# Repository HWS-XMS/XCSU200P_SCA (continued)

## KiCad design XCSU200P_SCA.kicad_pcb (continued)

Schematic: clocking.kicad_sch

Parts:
C1001, C1002, C1003, C1004, C1005, C1009, C1012, C1015, C1018: 100n; C_0402_1005Metric; MPN Samsung CL05B104KO5NNNC, 16 V X7R; LCSC C1525
C1006: 100n; C_0402_1005Metric; MPN Samsung CL05B104KO5NNNC, 16 V X7R; LCSC C1525; not fitted
C1007, C1010, C1013, C1016: 4u7; C_0603_1608Metric; MPN Samsung CL10A475KO8NNNC, 16 V X5R; LCSC C19666
C1008, C1011, C1014, C1017: 470n; C_0402_1005Metric; MPN Samsung CL05A474KP5NNNC, 10 V X5R; LCSC C47339
D1001: BAT54; D_SOD-323; MPN onsemi BAT54HT1G; LCSC C21107
FB1001, FB1002, FB1003, FB1004: 600R@100MHz; L_0603_1608Metric; MPN Sunlord GZ1608D601TF, 200 mA; LCSC C1002
J1001: REF IN; SMA_Molex_73251-2200_Horizontal_Drill1.6mm; MPN Lian Xin SMA-KWE; LCSC C7498154
J1002: REF OUT; SMA_Molex_73251-2200_Horizontal_Drill1.6mm; MPN Lian Xin SMA-KWE; LCSC C7498154
JP1001: 50R term; PinHeader_1x02_P2.54mm_Vertical; MPN XFCN PZ254V-11-02P; LCSC C492401
JP1002: REFSEL = H; PinHeader_1x02_P2.54mm_Vertical; MPN XFCN PZ254V-11-02P; LCSC C492401
JP1003: HW_SW_CTRL; PinHeader_1x03_P2.54mm_Vertical; MPN BOOMELE 2.54-1*3P; LCSC C49257
JP1004: REF / FPGA; PinHeader_1x03_P2.54mm_Vertical; MPN BOOMELE 2.54-1*3P; LCSC C49257
R1001: 49R9 1W; R_2512_6332Metric; MPN UNI-ROYAL 25121WF499JT4E, 1 W; LCSC C25487
R1002: 330R; R_0402_1005Metric; MPN UNI-ROYAL 0402WGF3300TCE; LCSC C25104
R1003: 12k; R_0402_1005Metric; MPN UNI-ROYAL 0402WGF1202TCE; LCSC C25752
R1004, R1007, R1018: 10k; R_0402_1005Metric; MPN UNI-ROYAL 0402WGF1002TCE; LCSC C25744
R1005, R1008, R1009: 33R; R_0402_1005Metric; MPN UNI-ROYAL 0402WGF330JTCE; LCSC C25105
R1006: 100k; R_0402_1005Metric; MPN UNI-ROYAL 0402WGF1003TCE; LCSC C25741
R1010, R1011: 10R; R_0402_1005Metric; MPN UNI-ROYAL 0402WGF100JTCE; LCSC C25077
R1012: 100R; R_0402_1005Metric; MPN UNI-ROYAL 0402WGF1000TCE; LCSC C25076; not fitted
R1013, R1014, R1015: 1k; R_0402_1005Metric; MPN UNI-ROYAL 0402WGF1001TCE; LCSC C11702
R1016, R1017: 4k7; R_0402_1005Metric; MPN UNI-ROYAL 0402WGF4701TCE; LCSC C25900
R1019: 47R; R_0402_1005Metric; MPN UNI-ROYAL 0402WGF470JTCE; LCSC C25118
R1020: 100R; R_0402_1005Metric; MPN UNI-ROYAL 0402WGF1000TCE; LCSC C25076
SW1001: TCXO / EXT; SW_SPDT_Shouhan_MSK12C02; LCSC C431540
TP1001: OUT0; TestPoint_Keystone_5005-5009_Compact_NoCircle; MPN Keystone 5008 (orange)
TP1002: OUT1_N; TestPoint_Keystone_5005-5009_Compact_NoCircle; MPN Keystone 5008 (orange)
TP1003: OUT4_N; TestPoint_Keystone_5005-5009_Compact_NoCircle; MPN Keystone 5008 (orange)
TP1004: REF_CLK; TestPoint_Keystone_5005-5009_Compact_NoCircle; MPN Keystone 5008 (orange)
TP1005: GND; TestPoint_Keystone_5005-5009_Compact_NoCircle; MPN Keystone 5006 (black); LCSC C2906764
U1001: 74LVC1G17; SOT-23-5; LCSC C7836
U1002: 74LVC1G157; SOT-363_SC-70-6; MPN Nexperia 74LVC1G157GW,125; LCSC C135822
U1003: CDCE6214RGER; Texas_RGE0024P_VQFN-24-1EP_4x4mm_P0.5mm_EP2.7x2.7mm_Thermal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; LCSC C3608351
U1004: 74LVC1G125; SOT-23-5; MPN TI SN74LVC1G125DBVR; LCSC C23654
Y1001: ECS-TXO-3225MV-100; Oscillator_SMD_ECS_TXO-3225MV_3.2x2.5mm; LCSC C2442721

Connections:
+1V8: FB1002.1, FB1003.1, FB1004.1; also elsewhere on the board
+3V3_CLK: C1002.1, C1003.1, C1004.1, C1005.1, FB1001.1, R1003.1, R1007.1, SW1001.1 (A), U1001.5 (VCC), U1002.5 (VCC), U1004.5 (VCC), Y1001.4 (VDD); also elsewhere on the board
/Clocking/CLK_A: R1010.2; also elsewhere on the board
/Clocking/CLK_B: R1011.2; also elsewhere on the board
/Clocking/CLK_LVDS_N: R1012.2, U1003.13 (OUT3_N); also elsewhere on the board
/Clocking/CLK_LVDS_P: R1012.1, U1003.14 (OUT3_P); also elsewhere on the board
/Clocking/PLL_GPIO1: R1014.1; also elsewhere on the board
/Clocking/PLL_GPIO4: R1015.1; also elsewhere on the board
/Clocking/PLL_RESET_N: R1013.1; also elsewhere on the board
/Clocking/REFOUT_FPGA: JP1004.3 (B); also elsewhere on the board
/Clocking/REF_10M: R1008.2; also elsewhere on the board
/Clocking/REF_CLK: JP1004.1 (A), R1008.1, R1009.1, R1020.1, U1002.4 (Y)
/Clocking/REF_SEL: R1007.2, SW1001.2 (B), U1002.6 (S), Y1001.1 (EN)
/PLL_SCL: R1016.2, U1003.12 (SCL/GPIO3); also elsewhere on the board
/PLL_SDA: R1017.2, U1003.19 (SDA/GPIO2); also elsewhere on the board
GND: C1002.2, C1003.2, C1004.2, C1005.2, C1006.2, C1007.2, C1008.2, C1009.2, C1010.2, C1011.2, C1012.2, C1013.2, C1014.2, C1015.2, C1016.2, C1017.2, C1018.2, D1001.2 (A), J1001.2 (Ext), J1002.2 (Ext), JP1003.1 (A), R1001.2, R1004.2, R1006.2, R1018.2, SW1001.3 (C), TP1005.1 (1_1), U1001.3 (GND), U1002.2 (GND), U1003.6 (PRIREF_N), U1003.25 (GND), U1004.1, U1004.3 (GND), Y1001.2 (GND); also elsewhere on the board
unnamed: C1001.2, R1002.1
unnamed: D1001.1 (K), R1002.2, R1003.2, R1004.1, U1001.2
unnamed: C1001.1, J1001.1 (In), JP1001.1 (A)
unnamed: J1002.1 (In), R1019.2
unnamed: JP1001.2 (B), R1001.1
unnamed: JP1002.2 (B), U1003.4 (REFSEL)
unnamed: JP1003.2 (C), U1003.23 (HW_SW_CTRL)
unnamed: JP1004.2 (C), R1018.1, U1004.2
unnamed: R1019.1, U1004.4
unnamed: R1020.2, TP1004.1 (1_1)
unnamed: U1001.4, U1002.3 (I0)
unnamed: R1005.2, R1006.1, U1002.1 (I1)
unnamed: R1014.2, U1003.20 (GPIO1)
unnamed: R1015.2, U1003.11 (GPIO4)
unnamed: TP1001.1 (1_1), U1003.7 (OUT0)
unnamed: TP1002.1 (1_1), U1003.21 (OUT1_N)
unnamed: R1010.1, U1003.22 (OUT1_P)
unnamed: TP1003.1 (1_1), U1003.9 (OUT4_N)
unnamed: R1011.1, U1003.10 (OUT4_P)
unnamed: C1006.1, R1013.2, U1003.8 (PDN)
unnamed: R1009.2, U1003.5 (PRIREF_P)
unnamed: R1005.1, Y1001.3 (OUT)
VDDO_12: C1013.1, C1014.1, C1015.1, FB1003.2, U1003.16 (VDDO_12)
VDDO_34: C1016.1, C1017.1, C1018.1, FB1004.2, U1003.15 (VDDO_34)
VDD_REF: C1007.1, C1008.1, C1009.1, FB1001.2, JP1002.1 (A), JP1003.3 (B), R1016.1, R1017.1, U1003.3 (VDD_REF)
VDD_VCO: C1010.1, C1011.1, C1012.1, FB1002.2, U1003.24 (VDD_VCO)

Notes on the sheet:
REF IN: 10 MHz, LVCMOS (3.3 V / 5 V) or sine >= +7 dBm
Bias at the middle of the Schmitt thresholds: a sine also switches the buffer.
10 MHz TCXO and reference source select
REF_SEL high: TCXO. Low: REF IN, TCXO output off (high-Z). REF_CLK is the selected reference: the PLL locks to it, REF OUT is a buffered copy of it.
CDCE6214: outputs locked to REF_CLK (PRIREF); programmed by the FPGA over I2C
Test loops
Straps (tri-level pins). REFSEL high: PRIREF. HW_SW_CTRL open: fall-back mode with I2C, for the first programming; 1-2: EEPROM page 0, 2-3: page 1. PDN capacitor: fit if the reset must outlast the supply ramp.
100R: only if the FPGA's internal termination is not used.
1.8 V LVCMOS
REF OUT: 3.3 V LVCMOS, 10 MHz
PLL supplies: VDD_REF 3.3 V, VCO and outputs 1.8 V

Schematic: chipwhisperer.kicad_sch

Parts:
C1101, C1102, C1103, C1104: 100n; C_0402_1005Metric; MPN Samsung CL05B104KO5NNNC, 16 V X7R; LCSC C1525
D1101, D1102, D1103: SRV05-4; SOT-23-6; MPN Semtech SRV05-4.TCT; LCSC C13612
J1101: CW 20-pin; IDC-Header_2x10_P2.54mm_Vertical; MPN XFCN BH254V-20P; LCSC C492444
JP1101: VREF; PinHeader_1x02_P2.54mm_Vertical; MPN XFCN PZ254V-11-02P; LCSC C492401
R1101, R1102, R1103, R1104, R1105, R1106, R1107, R1108, R1109, R1110, R1111, R1112: 22R; R_0402_1005Metric; MPN UNI-ROYAL 0402WGF220JTCE; LCSC C25092
R1113, R1114, R1115: 4k7; R_0402_1005Metric; MPN UNI-ROYAL 0402WGF4701TCE; LCSC C25900
R1116, R1117: 10k; R_0402_1005Metric; MPN UNI-ROYAL 0402WGF1002TCE; LCSC C25744
R1118, R1119, R1120: 33R; R_0402_1005Metric; MPN UNI-ROYAL 0402WGF330JTCE; LCSC C25105
R1121: 330R; R_0402_1005Metric; MPN UNI-ROYAL 0402WGF3300TCE; LCSC C25104
R1122, R1123: 100R; R_0402_1005Metric; MPN UNI-ROYAL 0402WGF1000TCE; LCSC C25076
R1124, R1126, R1127, R1128: 1k; R_0402_1005Metric; MPN UNI-ROYAL 0402WGF1001TCE; LCSC C11702
R1125: 220R; R_0402_1005Metric; MPN UNI-ROYAL 0402WGF2200TCE; LCSC C25091
SW1101: JTAG-OFF-SERIAL; SW_SP3T_Shouhan_MSK13C02_Edge; MPN Shouhan MSK13C02; LCSC C2681567
U1101, U1102: 74LVC125; TSSOP-14_4.4x5mm_P0.65mm; MPN TI SN74LVC125APWR; LCSC C7813
U1103: SN74LV4T125; TSSOP-14_4.4x5mm_P0.65mm; MPN TI SN74LV4T125PWR; LCSC C90755

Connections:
+1V8: C1102.1, C1103.1, R1116.1, R1117.1, U1101.13, U1101.14 (VCC), U1102.14 (VCC); also elsewhere on the board
+3V3: C1104.1, JP1101.2 (B), R1113.1, R1114.1, U1103.14 (VCC); also elsewhere on the board
/CW_JTAG_SEL_N: R1116.2, SW1101.1, U1101.1, U1101.4, U1101.10, U1103.1; also elsewhere on the board
/ChipWhisperer/CFG_CCLK: R1121.2; also elsewhere on the board
/ChipWhisperer/CFG_CS_B: R1123.2; also elsewhere on the board
/ChipWhisperer/CFG_DIN: R1122.2; also elsewhere on the board
/ChipWhisperer/CFG_READY: U1103.12; also elsewhere on the board
/ChipWhisperer/CWH_HS1: D1101.1 (IO1), J1101.4 (HS1), R1101.1
/ChipWhisperer/CWH_HS2: D1101.4 (IO3), J1101.6 (HS2), R1103.1
/ChipWhisperer/CWH_MISO: D1101.6 (IO4), J1101.7 (MISO), R1104.1
/ChipWhisperer/CWH_MOSI: D1102.1 (IO1), J1101.9 (MOSI), R1105.1
/ChipWhisperer/CWH_NRST: D1101.3 (IO2), J1101.5 (NRST), R1102.1
/ChipWhisperer/CWH_PDIC: D1103.1 (IO1), J1101.13 (PDIC), R1109.1
/ChipWhisperer/CWH_PDID: D1103.4 (IO3), J1101.15 (PDID), R1111.1
/ChipWhisperer/CWH_SCK: D1102.4 (IO3), J1101.11 (SCK), R1107.1
/ChipWhisperer/CWH_TIO1: D1102.3 (IO2), J1101.10 (TIO1), R1106.1
/ChipWhisperer/CWH_TIO2: D1102.6 (IO4), J1101.12 (TIO2), R1108.1
/ChipWhisperer/CWH_TIO3: D1103.3 (IO2), J1101.14 (TIO3), R1110.1
/ChipWhisperer/CWH_TIO4: D1103.6 (IO4), J1101.16 (TIO4), R1112.1
/ChipWhisperer/CW_HS1: R1101.2; also elsewhere on the board
/ChipWhisperer/CW_HS2: R1103.2; also elsewhere on the board
/ChipWhisperer/CW_MISO: R1104.2, R1125.2; also elsewhere on the board
/ChipWhisperer/CW_MOSI: R1105.2, U1101.5, U1102.5; also elsewhere on the board
/ChipWhisperer/CW_NRST: R1102.2; also elsewhere on the board
/ChipWhisperer/CW_PDIC: R1109.2, R1113.2, U1102.12; also elsewhere on the board
/ChipWhisperer/CW_PDID: R1111.2, R1114.2, U1101.9, U1102.9; also elsewhere on the board
/ChipWhisperer/CW_SCK: R1107.2, R1115.1, U1101.2, U1102.2; also elsewhere on the board
/ChipWhisperer/CW_SER_SEL_N: R1117.2, SW1101.4, U1102.1, U1102.4, U1102.10, U1102.13, U1103.4, U1103.10, U1103.13
/ChipWhisperer/CW_TIO1: R1106.2, R1127.2; also elsewhere on the board
/ChipWhisperer/CW_TIO2: R1108.2; also elsewhere on the board
/ChipWhisperer/CW_TIO3: R1110.2, R1126.2; also elsewhere on the board
/ChipWhisperer/ESD_REF: C1101.1, D1101.5 (VP), D1102.5 (VP), D1103.5 (VP)
/FPGA banks 3.3 V/CW_TIO4: R1112.2, R1128.2; also elsewhere on the board
/FPGA configuration/DONE: U1103.9; also elsewhere on the board
/FPGA configuration/INIT_B: U1103.5; also elsewhere on the board
/FPGA configuration/PROGRAM_B: R1124.2; also elsewhere on the board
/JTAG_TCK: R1118.2; also elsewhere on the board
/JTAG_TDI: R1119.2; also elsewhere on the board
/JTAG_TDO: U1103.2; also elsewhere on the board
/JTAG_TMS: R1120.2; also elsewhere on the board
GND: C1101.2, C1102.2, C1103.2, C1104.2, D1101.2 (VN), D1102.2 (VN), D1103.2 (VN), J1101.2 (GND), J1101.17 (GND), J1101.19 (GND), R1115.2, SW1101.3, U1101.7 (GND), U1101.12, U1102.7 (GND), U1103.7 (GND); also elsewhere on the board
unnamed: J1101.8 (VREF), JP1101.1 (A)
unnamed: R1118.1, U1101.3
unnamed: R1119.1, U1101.6
unnamed: R1120.1, U1101.8
unnamed: R1121.1, U1102.3
unnamed: R1122.1, U1102.6
unnamed: R1123.1, U1102.8
unnamed: R1124.1, U1102.11
unnamed: R1125.1, U1103.3
unnamed: R1126.1, U1103.6
unnamed: R1127.1, U1103.8
unnamed: R1128.1, U1103.11

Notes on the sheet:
ChipWhisperer 20-pin target connector: ESD protection, 22R, ports to the FPGA (bank 44)
VREF to 3.3 V as on the CW305; remove the jumper if the capture device drives it.
HS1: clock from the FPGA to the capture device. HS2: clock from the capture device.
Status and TDO to the capture device (1.8 V -> 3.3 V)
JTAG and slave serial from the capture device (3.3 V -> 1.8 V)
Configuration source selector: JTAG / OFF / SERIAL
OFF: the connector reaches only the FPGA user pins (CW305 behaviour). JTAG: the capture device drives the FPGA TAP (SCK = TCK, MOSI = TDI, PDID = TMS, MISO = TDO); the FT4232H JTAG buffers are disabled by CW_JTAG_SEL_N. TDO reaches MISO through 220R: keep the FPGA pin on CW_MISO an input in designs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
Buffer supplies and spare gate (disabled)
ESD arrays: rails
ESD_REF is not tied to +3V3: a powered capture device cannot feed the rail through the arrays.

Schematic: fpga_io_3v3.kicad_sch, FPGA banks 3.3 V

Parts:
C1201: 100n; C_0402_1005Metric; MPN Samsung CL05B104KO5NNNC, 16 V X7R; LCSC C1525
C1202: 47u; C_1206_3216Metric; MPN Samsung CL31A476MPHNNNE, 10 V X5R; LCSC C96123
C1203, C1204, C1205: 10u; C_0603_1608Metric; MPN Samsung CL10A106KP8NNNC, 10 V X5R; LCSC C19702
C1206, C1207, C1208: 1u; C_0402_1005Metric; MPN Samsung CL05A105KA5NQNC, 25 V X5R; LCSC C52923
D1201, D1202, D1203, D1204: green; LED_0603_1608Metric; MPN Lite-On LTST-C191KGKT, 2 V; LCSC C125098
J1201: 3V3 I/O; PinHeader_2x10_P2.54mm_Vertical; MPN XFCN PZ254V-12-20P; LCSC C492427
R1201, R1202, R1203, R1204: 330R; R_0402_1005Metric; MPN UNI-ROYAL 0402WGF3300TCE; LCSC C25104
R1205: 10k; R_0402_1005Metric; MPN UNI-ROYAL 0402WGF1002TCE; LCSC C25744
R1206: 100R; R_0402_1005Metric; MPN UNI-ROYAL 0402WGF1000TCE; LCSC C25076
R1207: 1k; R_0402_1005Metric; MPN UNI-ROYAL 0402WGF1001TCE; LCSC C11702
SW1201: RESET; SW_Push_1P1T_XKB_TS-1187A; MPN XKB TS-1187A-B-A-B; LCSC C318884
TP1201: TRIGGER; TestPoint_Keystone_5005-5009_Compact_NoCircle; MPN Keystone 5008 (orange)
TP1202: GND; TestPoint_Keystone_5005-5009_Compact_NoCircle; MPN Keystone 5006 (black); LCSC C2906764
U1: XCSU200P-SBVA1024; AMD_SBVA1024_BGA-1024_27.0x27.0mm_Layout32x32_P0.8mm

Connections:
+3V3: C1202.1, C1203.1, C1204.1, C1205.1, C1206.1, C1207.1, C1208.1, J1201.2, J1201.20, SW1201.2, U1.AA24 (VCCO_43), U1.AA25 (VCCO_44), U1.AB25 (VCCO_44), U1.AC24 (VCCO_43), U1.AE24 (VCCO_43), U1.J18 (VCCO_65), U1.K17 (VCCO_65), U1.K18 (VCCO_65), U1.P19 (VCCO_65), U1.U22 (VCCO_44), U1.W22 (VCCO_43), U1.W24 (VCCO_44); also elsewhere on the board
/ChipWhisperer/CW_HS1: U1.AB32 (IO_L28P_44); also elsewhere on the board
/ChipWhisperer/CW_HS2: U1.AD29 (IO_L23P_HDGC_44); also elsewhere on the board
/ChipWhisperer/CW_MISO: U1.AG32 (IO_L42P_44); also elsewhere on the board
/ChipWhisperer/CW_MOSI: U1.AH32 (IO_L42N_44); also elsewhere on the board
/ChipWhisperer/CW_NRST: U1.AM30 (IO_L36P_44); also elsewhere on the board
/ChipWhisperer/CW_PDIC: U1.AK32 (IO_L40N_44); also elsewhere on the board
/ChipWhisperer/CW_PDID: U1.AL32 (IO_L38N_44); also elsewhere on the board
/ChipWhisperer/CW_SCK: U1.AJ32 (IO_L40P_44); also elsewhere on the board
/ChipWhisperer/CW_TIO1: U1.AC32 (IO_L28N_44); also elsewhere on the board
/ChipWhisperer/CW_TIO2: U1.AD32 (IO_L26N_44); also elsewhere on the board
/ChipWhisperer/CW_TIO3: U1.AE32 (IO_L35N_44); also elsewhere on the board
/Clocking/PLL_GPIO1: U1.AJ26 (IO_L16N_43); also elsewhere on the board
/Clocking/PLL_GPIO4: U1.AJ27 (IO_L18P_43); also elsewhere on the board
/Clocking/PLL_RESET_N: U1.AJ28 (IO_L20P_43); also elsewhere on the board
/Clocking/REFOUT_FPGA: U1.AK29 (IO_L21P_43); also elsewhere on the board
/Clocking/REF_10M: U1.AF29 (IO_L7P_HDGC_43); also elsewhere on the board
/FPGA banks 3.3 V/BTN_RESET: C1201.1, R1205.1, R1207.1, U1.AK28 (IO_L20N_43)
/FPGA banks 3.3 V/CW_TIO4: R1206.1, U1.AE31 (IO_L35P_44); also elsewhere on the board
/FPGA banks 3.3 V/FIFO_AC8: U1.D20 (IO_L17P_PERSTN0_B_65); also elsewhere on the board
/FPGA banks 3.3 V/FIFO_AC9: U1.F17 (IO_L1N_D30_65); also elsewhere on the board
/FPGA banks 3.3 V/FIFO_CLK: U1.C18 (IO_L6P_HDGC_65); also elsewhere on the board
/FPGA banks 3.3 V/FIFO_D0: U1.A16 (IO_L9P_D21_65); also elsewhere on the board
/FPGA banks 3.3 V/FIFO_D1: U1.A17 (IO_L9N_D19_65); also elsewhere on the board
/FPGA banks 3.3 V/FIFO_D2: U1.B16 (IO_L3N_D22_65); also elsewhere on the board
/FPGA banks 3.3 V/FIFO_D3: U1.B17 (IO_L10N_D15_65); also elsewhere on the board
/FPGA banks 3.3 V/FIFO_D4: U1.C16 (IO_L3P_D24_65); also elsewhere on the board
/FPGA banks 3.3 V/FIFO_D5: U1.C17 (IO_L10P_D17_65); also elsewhere on the board
/FPGA banks 3.3 V/FIFO_D6: U1.D16 (IO_L8N_D23_65); also elsewhere on the board
/FPGA banks 3.3 V/FIFO_D7: U1.D17 (IO_L11N_D12_65); also elsewhere on the board
/FPGA banks 3.3 V/FIFO_OE_N: U1.C20 (IO_L21P_OSPI_RST_B_65); also elsewhere on the board
/FPGA banks 3.3 V/FIFO_RD_N: U1.C19 (IO_L18N_D10_OSPID06_65); also elsewhere on the board
/FPGA banks 3.3 V/FIFO_RXF_N: U1.A18 (IO_L20P_D06_OSPID02_65); also elsewhere on the board
/FPGA banks 3.3 V/FIFO_SIWU_N: U1.A20 (IO_L15N_CSI_B_65); also elsewhere on the board
/FPGA banks 3.3 V/FIFO_TXE_N: U1.A19 (IO_L20N_D04_OSPID00_65); also elsewhere on the board
/FPGA banks 3.3 V/FIFO_WR_N: U1.D19 (IO_L18P_D11_OSPID07_65); also elsewhere on the board
/FPGA banks 3.3 V/HDR3V3_IO0: J1201.1, U1.AL23 (IO_L10P_43)
/FPGA banks 3.3 V/HDR3V3_IO1: J1201.3, U1.AM23 (IO_L10N_43)
/FPGA banks 3.3 V/HDR3V3_IO2: J1201.5, U1.AL24 (IO_L4P_43)
/FPGA banks 3.3 V/HDR3V3_IO3: J1201.7, U1.AM24 (IO_L4N_43)
/FPGA banks 3.3 V/HDR3V3_IO4: J1201.9, U1.AL25 (IO_L8P_43)
/FPGA banks 3.3 V/HDR3V3_IO5: J1201.11, U1.AM26 (IO_L8N_43)
/FPGA banks 3.3 V/HDR3V3_IO6: J1201.13, U1.AL27 (IO_L11P_43)
/FPGA banks 3.3 V/HDR3V3_IO7: J1201.15, U1.AM27 (IO_L11N_43)
/FPGA banks 3.3 V/HDR3V3_IO8: J1201.17, U1.AM28 (IO_L19P_43)
/FPGA banks 3.3 V/HDR3V3_IO9: J1201.19, U1.AM29 (IO_L19N_43)
/FPGA banks 3.3 V/LED0: R1201.1, U1.AK23 (IO_L3P_43)
/FPGA banks 3.3 V/LED1: R1202.1, U1.AK24 (IO_L3N_43)
/FPGA banks 3.3 V/LED2: R1203.1, U1.AK26 (IO_L17P_43)
/FPGA banks 3.3 V/LED3: R1204.1, U1.AK27 (IO_L18N_43)
/FPGA banks 3.3 V/UART_CTS_N: U1.E17 (IO_L11P_D13_65); also elsewhere on the board
/FPGA banks 3.3 V/UART_RTS_N: U1.F20 (IO_L14N_BUSY_65); also elsewhere on the board
/FPGA banks 3.3 V/UART_RXD: U1.B21 (IO_L21N_OSPI_ECC_FAIL_65); also elsewhere on the board
/FPGA banks 3.3 V/UART_TXD: U1.E16 (IO_L8P_D25_65); also elsewhere on the board
/PLL_SCL: U1.AJ24 (IO_L15P_43); also elsewhere on the board
/PLL_SDA: U1.AJ25 (IO_L15N_43); also elsewhere on the board
GND: C1201.2, C1202.2, C1203.2, C1204.2, C1205.2, C1206.2, C1207.2, C1208.2, D1201.1 (K), D1202.1 (K), D1203.1 (K), D1204.1 (K), J1201.4, J1201.6, J1201.8, J1201.10, J1201.12, J1201.14, J1201.16, J1201.18, R1205.2, TP1202.1 (1_1); also elsewhere on the board
unnamed: D1201.2 (A), R1201.2
unnamed: D1202.2 (A), R1202.2
unnamed: D1203.2 (A), R1203.2
unnamed: D1204.2 (A), R1204.2
unnamed: R1206.2, TP1201.1 (1_1)
unnamed: R1207.2, SW1201.1

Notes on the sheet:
Bank 65: FT232H FIFO, UART
Bank 44: ChipWhisperer 20-pin
Bank 43: 3.3 V header, LEDs, button
3.3 V header
User LEDs (active high)
Push-button (active high, usable as reset)
Test loops
VCCO decoupling, banks 43/44/65

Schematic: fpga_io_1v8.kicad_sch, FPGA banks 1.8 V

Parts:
C1301: 47u; C_1206_3216Metric; MPN Samsung CL31A476MPHNNNE, 10 V X5R; LCSC C96123
C1302, C1303: 10u; C_0603_1608Metric; MPN Samsung CL10A106KP8NNNC, 10 V X5R; LCSC C19702
C1304, C1305: 1u; C_0402_1005Metric; MPN Samsung CL05A105KA5NQNC, 25 V X5R; LCSC C52923
J1301: 1V8 I/O; PinHeader_2x10_P2.54mm_Vertical; MPN XFCN PZ254V-12-20P; LCSC C492427
R1301, R1302: 1k; R_0402_1005Metric; MPN UNI-ROYAL 0402WGF1001TCE; LCSC C11702
U1: XCSU200P-SBVA1024; AMD_SBVA1024_BGA-1024_27.0x27.0mm_Layout32x32_P0.8mm

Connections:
+1V8: C1301.1, C1302.1, C1303.1, C1304.1, C1305.1, J1301.2, J1301.20, U1.L24 (VCCO_46), U1.M25 (VCCO_46), U1.N23 (VCCO_46), U1.N24 (VCCO_46), U1.R24 (VCCO_45), U1.T25 (VCCO_45), U1.U24 (VCCO_45), U1.V25 (VCCO_45); also elsewhere on the board
/Clocking/CLK_A: U1.T31 (IO_L14P_T2L_N2_GC_45); also elsewhere on the board
/Clocking/CLK_B: U1.T29 (IO_L13P_T2L_N0_GC_QBC_45); also elsewhere on the board
/Clocking/CLK_LVDS_N: U1.U28 (IO_L12N_T1U_N11_GC_45); also elsewhere on the board
/Clocking/CLK_LVDS_P: U1.V28 (IO_L12P_T1U_N10_GC_45); also elsewhere on the board
/FPGA banks 1.8 V/HDR1V8_IO0: J1301.1, U1.N32 (IO_L23P_T3U_N8_45)
/FPGA banks 1.8 V/HDR1V8_IO1: J1301.3, U1.M32 (IO_L23N_T3U_N9_45)
/FPGA banks 1.8 V/HDR1V8_IO2: J1301.5, U1.R32 (IO_L16P_T2U_N6_QBC_45)
/FPGA banks 1.8 V/HDR1V8_IO3: J1301.7, U1.P32 (IO_L16N_T2U_N7_QBC_45)
/FPGA banks 1.8 V/HDR1V8_IO4: J1301.9, U1.W32 (IO_L8P_T1L_N2_45)
/FPGA banks 1.8 V/HDR1V8_IO5: J1301.11, U1.V32 (IO_L8N_T1L_N3_45)
/FPGA banks 1.8 V/HDR1V8_IO6: J1301.13, U1.N31 (IO_L18P_T2U_N10_45)
/FPGA banks 1.8 V/HDR1V8_IO7: J1301.15, U1.M31 (IO_L18N_T2U_N11_45)
/FPGA banks 1.8 V/HDR1V8_IO8: J1301.17, U1.Y31 (IO_L7P_T1L_N0_QBC_45)
/FPGA banks 1.8 V/HDR1V8_IO9: J1301.19, U1.Y32 (IO_L7N_T1L_N1_QBC_45)
GND: C1301.2, C1302.2, C1303.2, C1304.2, C1305.2, J1301.4, J1301.6, J1301.8, J1301.10, J1301.12, J1301.14, J1301.16, J1301.18, R1301.2, R1302.2; also elsewhere on the board
unnamed: R1301.1, U1.R25 (VREF_45)
unnamed: R1302.1, U1.L25 (VREF_46)

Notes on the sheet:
Bank 45: PLL clocks, 1.8 V header (1.8 V max. on every pin)
Bank 46: not used
VREF pins to GND through 1k: the internal VREF is used (UG861).
1.8 V header
VCCO decoupling, banks 45/46

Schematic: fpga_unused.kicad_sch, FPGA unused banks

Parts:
C1401: 47u; C_1206_3216Metric; MPN Samsung CL31A476MPHNNNE, 10 V X5R; LCSC C96123
C1402, C1403, C1404, C1405, C1406, C1407: 10u; C_0603_1608Metric; MPN Samsung CL10A106KP8NNNC, 10 V X5R; LCSC C19702
C1408, C1409: 1u; C_0402_1005Metric; MPN Samsung CL05A105KA5NQNC, 25 V X5R; LCSC C52923
R1401: 240R 1%; R_0402_1005Metric; MPN UNI-ROYAL 0402WGF2400TCE; LCSC C25094
U1: XCSU200P-SBVA1024; AMD_SBVA1024_BGA-1024_27.0x27.0mm_Layout32x32_P0.8mm

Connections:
+1V2: C1406.1, C1407.1, C1408.1, C1409.1, R1401.1, U1.J12 (VCCO_86), U1.K10 (VCCO_86), U1.L10 (VCCO_86), U1.M8 (VCCO_85), U1.M9 (VCCO_86), U1.N8 (VCCO_85), U1.P9 (VCCO_85), U1.T9 (VCCO_85); also elsewhere on the board
+3V3: C1401.1, C1402.1, C1403.1, C1404.1, C1405.1, U1.AA22 (VCCO_42), U1.AB17 (VCCO_61), U1.AB19 (VCCO_61), U1.AB21 (VCCO_41), U1.AC20 (VCCO_61), U1.AC22 (VCCO_41), U1.AD19 (VCCO_42), U1.AD21 (VCCO_61), U1.AD23 (VCCO_41), U1.AE20 (VCCO_42), U1.AE22 (VCCO_41), U1.AF21 (VCCO_42), U1.K22 (VCCO_66), U1.K23 (VCCO_66), U1.L20 (VCCO_66), U1.L22 (VCCO_66); also elsewhere on the board
GND: C1401.2, C1402.2, C1403.2, C1404.2, C1405.2, C1406.2, C1407.2, C1408.2, C1409.2; also elsewhere on the board
unnamed: R1401.2, U1.L9 (VR_86)

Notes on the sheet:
Bank 41: not used, VCCO powered
Bank 42: not used, VCCO powered
Bank 61: not used, VCCO powered
Bank 66: not used, VCCO powered
Bank 85 (XP5IO): not used, VCCO = 1.2 V
Bank 86 (XP5IO): not used, VCCO = 1.2 V
VR_86 to VCCO_86 through 240R 1 % (UG861, required even if the bank is unused)
VCCO decoupling, banks 41/42/61/66
VCCO decoupling, banks 85/86

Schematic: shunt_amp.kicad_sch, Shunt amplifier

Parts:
C1501, C1502: 1u; C_0402_1005Metric; MPN Samsung CL05A105KA5NQNC, 25 V X5R; LCSC C52923
C1503, C1504, C1507, C1511, C1515, C1516: 10u; C_0603_1608Metric; MPN Samsung CL10A106KP8NNNC, 10 V X5R; LCSC C19702
C1505, C1509, C1513: 100n; C_0402_1005Metric; MPN Samsung CL05B104KO5NNNC, 16 V X7R; LCSC C1525
C1506: 10n; C_0402_1005Metric; MPN Samsung CL05B103KB5NNNC, 50 V X7R; LCSC C15195
C1508, C1512: 4u7; C_0603_1608Metric; MPN Samsung CL10A475KO8NNNC, 16 V X5R; LCSC C19666
C1510, C1514: 1n; C_0402_1005Metric; MPN FH 0402B102K500NT, 50 V X7R; LCSC C1523
D1501: BAT54S; SOT-23; MPN onsemi BAT54SLT1G; LCSC C19726
FB1501, FB1502: 600R@100MHz; L_0603_1608Metric; MPN Sunlord GZ1608D601TF, 200 mA; LCSC C1002
J1501: SHUNT x10; SMA_Molex_73251-2200_Horizontal_Drill1.6mm; MPN Lian Xin SMA-KWE; LCSC C7498154
J1502: SHUNT x100; SMA_Molex_73251-2200_Horizontal_Drill1.6mm; MPN Lian Xin SMA-KWE; LCSC C7498154
JP1501: AMP on; PinHeader_1x02_P2.54mm_Vertical; MPN XFCN PZ254V-11-02P; LCSC C492401
R1501: 100k; R_0402_1005Metric; MPN UNI-ROYAL 0402WGF1003TCE; LCSC C25741
R1502, R1503, R1504: 1k; R_0402_1005Metric; MPN UNI-ROYAL 0402WGF1001TCE; LCSC C11702
R1505: 24R9; R_0402_1005Metric; MPN UNI-ROYAL 0402WGF249JTCE; LCSC C5099
R1506, R1509: 240R; R_0402_1005Metric; MPN UNI-ROYAL 0402WGF2400TCE; LCSC C25094
R1507, R1510: 26R1; R_0402_1005Metric; MPN UNI-ROYAL 0402WGF261JTCE; LCSC C25098
R1508, R1511: 10k; R_0402_1005Metric; MPN UNI-ROYAL 0402WGF1002TCE; LCSC C25744
R1512: 22R; R_0402_1005Metric; MPN UNI-ROYAL 0402WGF220JTCE; LCSC C25092
R1513, R1514: 49R9; R_0402_1005Metric; MPN UNI-ROYAL 0402WGF499JTCE; LCSC C25120
R1515, R1516: 100R; R_0402_1005Metric; MPN UNI-ROYAL 0402WGF1000TCE; LCSC C25076
TP1501: LNA1; TestPoint_Keystone_5005-5009_Compact_NoCircle; MPN Keystone 5009 (yellow); LCSC C238126
TP1502: LNA2; TestPoint_Keystone_5005-5009_Compact_NoCircle; MPN Keystone 5009 (yellow); LCSC C238126
TP1503: GND; TestPoint_Keystone_5005-5009_Compact_NoCircle; MPN Keystone 5006 (black); LCSC C2906764
U1501: TPS7A2033PDBVR; SOT-23-5; LCSC C2862740
U1502, U1503: LMH6629SD; WSON-8-1EP_3x3mm_P0.5mm_EP1.6x2.0mm; LCSC C2060235

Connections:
+3V3_AMP: C1502.1, C1503.1, D1501.2 (K), FB1501.1, FB1502.1, R1502.1, U1501.5 (OUT)
/Shunt amplifier/LNA1_OUT: R1512.1, R1513.1, R1515.1, U1502.7 (OUT)
/Shunt amplifier/LNA2_OUT: R1514.1, R1516.1, U1503.7 (OUT)
/Shunt amplifier/VMID: C1504.1, C1505.1, R1502.2, R1503.1, R1504.1
GND: C1501.2, C1502.2, C1503.2, C1504.2, C1505.2, C1507.2, C1508.2, C1509.2, C1510.2, C1511.2, C1512.2, C1513.2, C1514.2, D1501.1 (A), J1501.2 (Ext), J1502.2 (Ext), R1501.2, R1503.2, TP1503.1 (1_1), U1501.2 (GND), U1502.5 (V-), U1502.9 (PAD), U1503.5 (V-), U1503.9 (PAD); also elsewhere on the board
unnamed: C1506.2, R1504.2, R1505.1
unnamed: C1507.1, R1507.2
unnamed: C1511.1, R1510.2
unnamed: C1515.1, R1513.2
unnamed: C1516.1, R1514.2
unnamed: D1501.3 (COM), R1505.2, U1502.4 (+IN)
unnamed: C1515.2, J1501.1 (In)
unnamed: C1516.2, J1502.1 (In)
unnamed: JP1501.2 (B), R1501.1, U1501.3 (EN)
unnamed: R1515.2, TP1501.1 (1_1)
unnamed: R1516.2, TP1502.1 (1_1)
unnamed: R1506.2, R1507.1, U1502.3 (-IN)
unnamed: C1508.1, C1509.1, C1510.1, FB1501.2, R1508.1, U1502.6 (COMP), U1502.8 (V+)
unnamed: R1506.1, U1502.2 (FB)
unnamed: R1508.2, U1502.1 (~PD)
unnamed: R1512.2, U1503.4 (+IN)
unnamed: R1509.2, R1510.1, U1503.3 (-IN)
unnamed: C1512.1, C1513.1, C1514.1, FB1502.2, R1511.1, U1503.6 (COMP), U1503.8 (V+)
unnamed: R1509.1, U1503.2 (FB)
unnamed: R1511.2, U1503.1 (~PD)
VCCINT: C1506.1; also elsewhere on the board
VPRE_3V8: C1501.1, JP1501.1 (A), U1501.1 (IN); also elsewhere on the board

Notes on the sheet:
Amplifier for the shunt path. It senses the FPGA side of the shunt (net VCCINT; Kelvin trace from the BGA side of the shunt), AC-coupled above 16 kHz. Two stages of x10: the outputs deliver x5 (14 dB) and x50 (34 dB) into a 50 ohm scope input; with the 20 mohm shunt about 0.15 V/A and 1.5 V/A at lo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
Amplifier supply
Stage 1
Input: 10 n / 1 k high-pass, 24R9 and clamp protect the input when the rail steps while the amplifier is off
Stage 2
Test loops
Guaranteed output swing: about +/-2.2 A of current swing at low frequency on x10 before clipping, +/-0.22 A on x100.

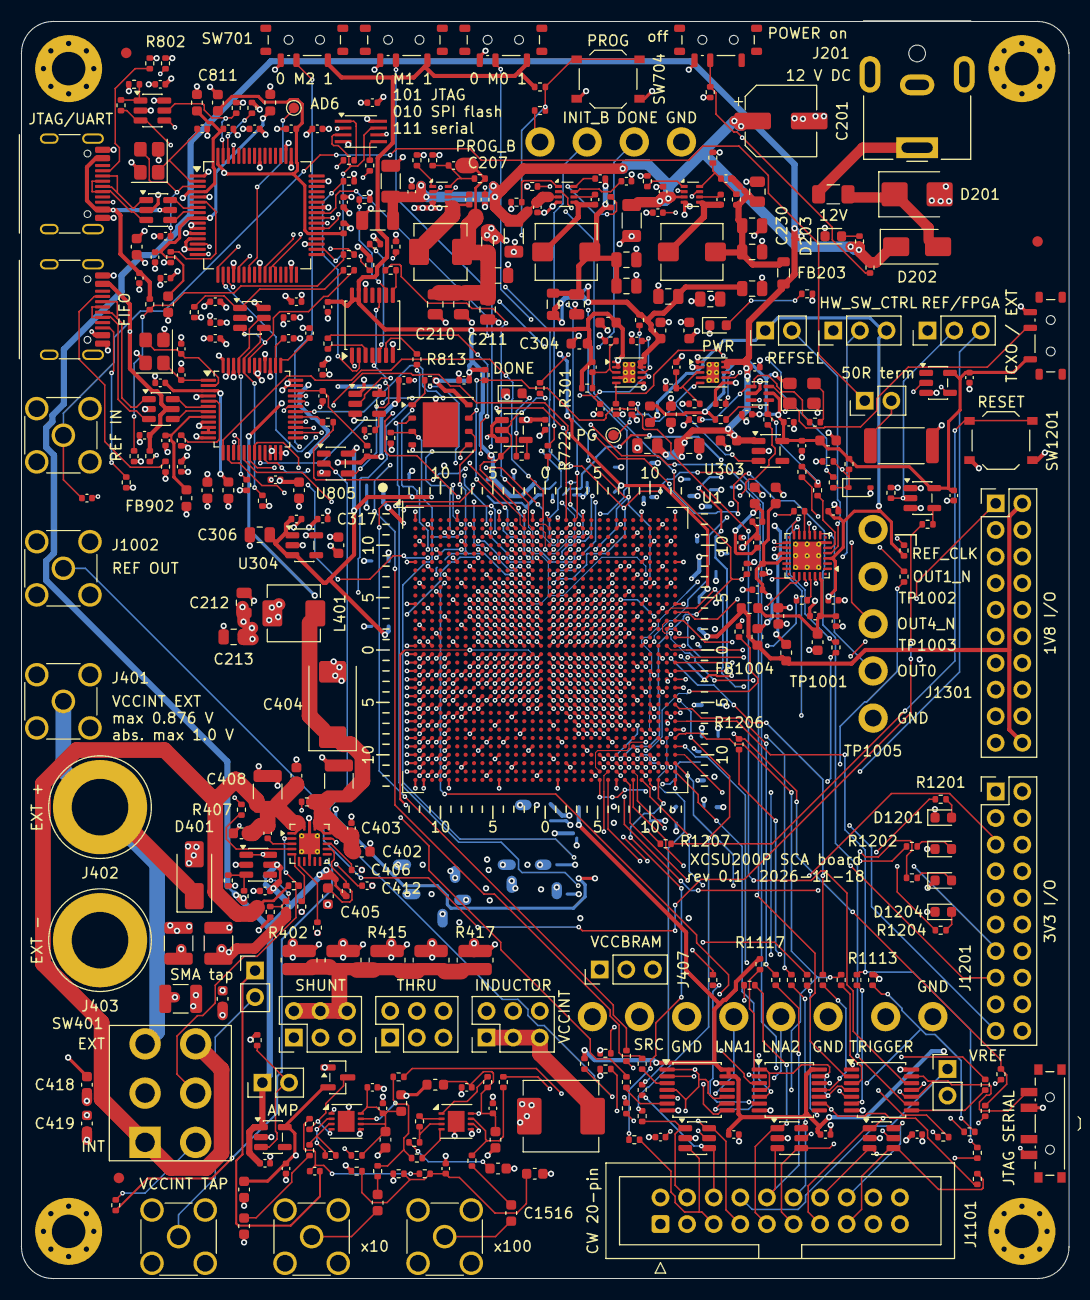
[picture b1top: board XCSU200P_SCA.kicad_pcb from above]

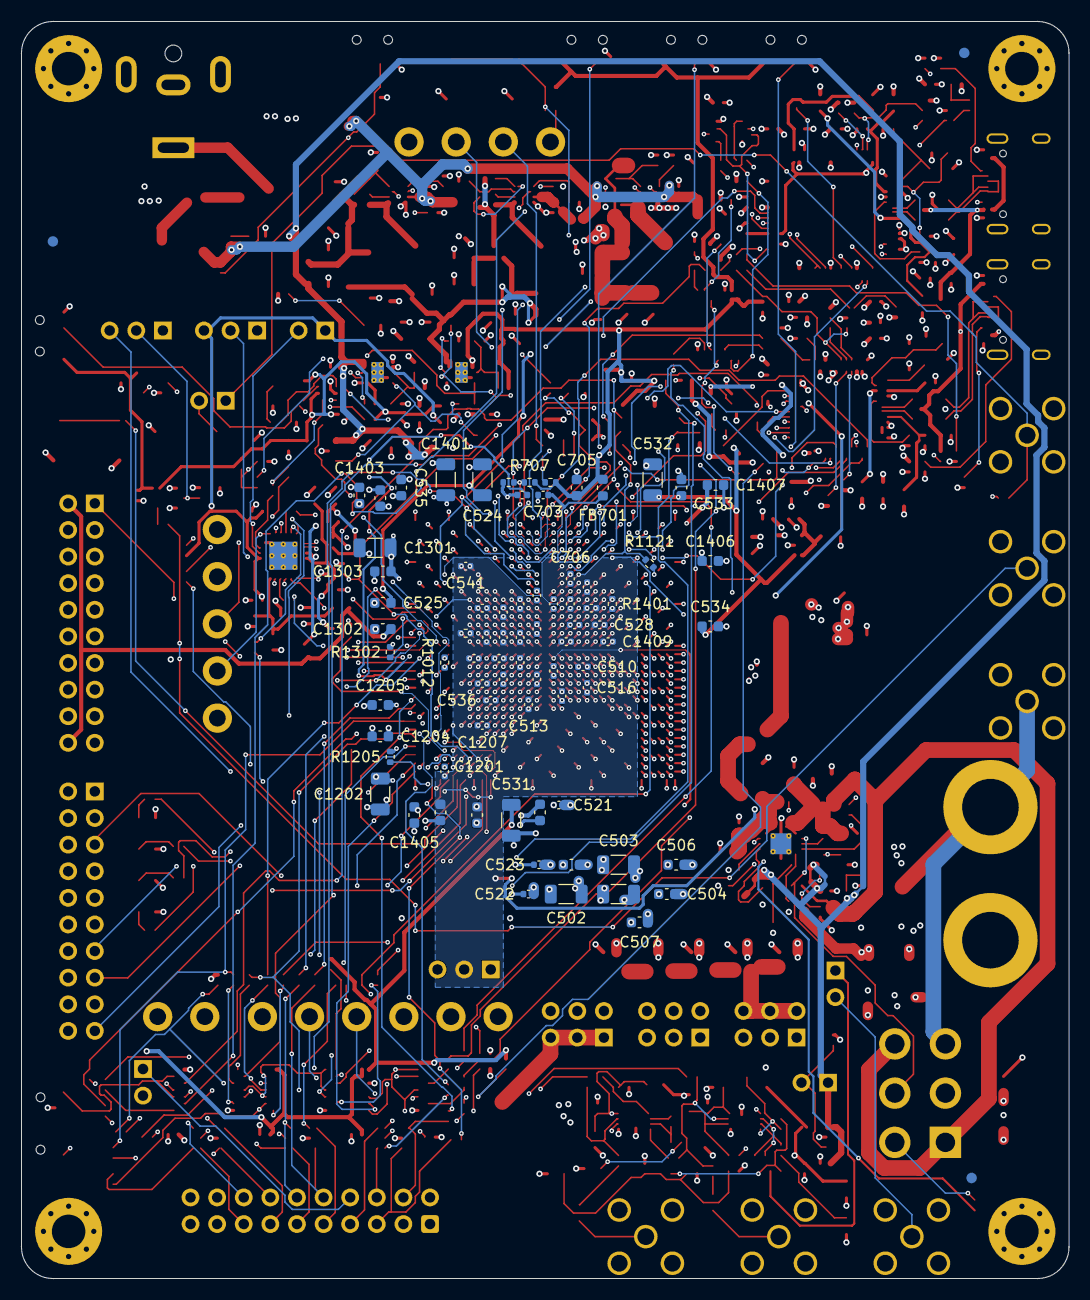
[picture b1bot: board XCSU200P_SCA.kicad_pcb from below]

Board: 6 copper layers, 100.0 x 120.0 mm, 499 parts (80 on the bottom side), 295 nets.

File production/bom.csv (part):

Designator,Footprint,Quantity,Value,LCSC Part #
"C1001, C1002, C1003, C1004, C1005, C1009, C1012, C1015, C1018, C1101, C1102, C1103, C1104, C1201, C1505, C1509, C1513, C302, C308, C403, C406, C411, C412, C413, C701, C702, C704, C801, C804, C805, C806, C807, C809, C812, C813, C814, C815, C816, C817, C818, C819, C820, C901, C905, C906, C907, C908, C909, C912, C913, C914, C915, C916",0402,53,100n,C1525
"C1007, C1010, C1013, C1016, C1508, C1512, C808, C810, C910, C911",0603,10,4u7,C19666
"C1008, C1011, C1014, C1017, C703",0402,5,470n,C47339
"C1202, C1301, C1401, C531, C532",1206,5,47u,C96123
"C1203, C1204, C1205, C1302, C1303, C1402, C1403, C1404, C1405, C1406, C1407, C1503, C1504, C1507, C1511, C1515, C1516, C301, C304, C305, C307, C310, C311, C315, C318, C402, C405, C409, C410, C417, C418, C419, C533, C534, C535, C705",0603,36,10u,C19702
"C1206, C1207, C1208, C1304, C1305, C1408, C1409, C1501, C1502, C313, C314, C316, C317, C536, C537, C538, C539, C540, C541, C706",0402,20,1u,C52923
"C1506, C303, C309, C407, C902",0402,5,10n,C15195
"C1510, C1514",0402,2,1n,C1523
C201,CP_Elec_6.3x7.7,1,100u 25V,C176675
"C202, C203, C214, C224",1206,4,10u 25V,C13585
"C204, C206, C215, C217, C225, C227",0402,6,100n 25V,C307331
"C205, C216, C226",0402,3,22n,C1532
"C208, C209, C210, C211, C212, C213, C219, C220, C221, C222, C223, C229, C230, C231, C232, C233",0805,16,22u,C45783
"C306, C312",0805,2,22u 10V,C45783
"C401, C408, C416",1210,3,47u,C77101
C404,CP_EIA-7343-20_Kemet-V,1,330u 25m,C79112
"C414, C415",1210,2,100u,C49066
"C802, C803, C903, C904",0402,4,27p,C1557
C811,0603,1,3u3,C51412
D1001,D_SOD-323,1,BAT54,C21107
"D1101, D1102, D1103",SOT-23-6,3,SRV05-4,C13612
"D1201, D1202, D1203, D1204",0603,4,green,C125098
D1501,SOT-23,1,BAT54S,C19726
D201,D_SMB,1,SMBJ15CA,C211759
D202,D_SMA,1,SS54,C22452
D203,0603,1,green 12V,C125098
D301,0603,1,green PWR,C125098
D401,D_SMA,1,SS34,C8678
D701,0603,1,blue DONE,C2288
"D801, D901",SOT-23-6,2,USBLC6-2SC6,C7519
F201,1206,1,4A fast,C187596
"FB1001, FB1002, FB1003, FB1004, FB1501, FB1502, FB701, FB801, FB802, FB901, FB902",0603,11,600R@100MHz,C1002
FB201,0805,1,120R 4A,C97001
"FB202, FB203",0805,2,1k 1.5A,C76817
J1001,SMA_Molex_73251-2200_Horizontal_Drill1.6mm,1,REF IN,C7498154
J1002,SMA_Molex_73251-2200_Horizontal_Drill1.6mm,1,REF OUT,C7498154
J1101,IDC-Header_2x10_P2.54mm_Vertical,1,CW 20-pin,C492444
J1201,PinHeader_2x10_P2.54mm_Vertical,1,3V3 I/O,C492427
J1301,PinHeader_2x10_P2.54mm_Vertical,1,1V8 I/O,C492427
J1501,SMA_Molex_73251-2200_Horizontal_Drill1.6mm,1,SHUNT x10,C7498154
J1502,SMA_Molex_73251-2200_Horizontal_Drill1.6mm,1,SHUNT x100,C7498154
J201,BarrelJack_CUI_PJ-063AH_Horizontal_Edge,1,"12 V DC, 5.5 / 2.1 mm",C22434582
J401,SMA_Molex_73251-2200_Horizontal_Drill1.6mm,1,VCCINT EXT,C7498154
J402,Banana_Jack_Keystone_575-4_Vertical,1,EXT +,C4944061
J403,Banana_Jack_Keystone_575-4_Vertical,1,EXT -,C4944061
J405,PinHeader_2x03_P2.54mm_Vertical,1,THRU,C492420
J406,PinHeader_2x03_P2.54mm_Vertical,1,SHUNT,C492420
J407,PinHeader_1x03_P2.54mm_Vertical,1,VCCBRAM,C49257
J408,PinHeader_2x03_P2.54mm_Vertical,1,INDUCTOR,C492420
J409,SMA_Molex_73251-2200_Horizontal_Drill1.6mm,1,VCCINT TAP,C7498154
"J801, J901",USB_C_Receptacle_HRO_TYPE-C-31-M-12_Edge,2,USB-C,C165948
JP1001,PinHeader_1x02_P2.54mm_Vertical,1,50R term,C492401
JP1002,PinHeader_1x02_P2.54mm_Vertical,1,REFSEL = H,C492401
JP1003,PinHeader_1x03_P2.54mm_Vertical,1,HW_SW_CTRL,C49257
JP1004,PinHeader_1x03_P2.54mm_Vertical,1,REF / FPGA,C49257
JP1101,PinHeader_1x02_P2.54mm_Vertical,1,VREF,C492401
JP1501,PinHeader_1x02_P2.54mm_Vertical,1,AMP on,C492401
JP401,PinHeader_1x02_P2.54mm_Vertical,1,SMA tap,C492401
L201,L_Changjiang_FXL0518,1,2u2,C475907
"L202, L203",L_Bourns_SRP5030T,2,6u8,C1329837
L401,L_Changjiang_FXL0518,1,1u 8A,C5298209
L402,L_Sunlord_MWSA0605S,1,10u 5A,C408467
R1001,2512,1,49R9 1W,C25487
"R1002, R1121, R1201, R1202, R1203, R1204, R815, R821, R822",0402,9,330R,C25104
R1003,0402,1,12k,C25752
"R1004, R1007, R1018, R1116, R1117, R1205, R1508, R1511, R305, R306, R405, R408, R410, R807, R808, R809, R810, R816, R817, R818, R905, R907, R908, R909",0402,24,10k,C25744
"R1005, R1008, R1009, R1118, R1119, R1120, R812, R813, R814",0402,9,33R,C25105
"R1006, R1501, R406",0402,3,100k,C25741
"R1010, R1011",0402,2,10R,C25077
"R1013, R1014, R1015, R1124, R1126, R1127, R1128, R1207, R1301, R1302, R1502, R1503, R1504, R307, R407, R708, R721, R722, R723, R805",0402,20,1k,C11702
"R1016, R1017, R1113, R1114, R1115, R203, R702, R703, R704, R705, R706, R820",0402,12,4k7,C25900
R1019,0402,1,47R,C25118
"R1020, R1122, R1123, R1206, R1515, R1516, R404, R709",0402,8,100R,C25076
"R1101, R1102, R1103, R1104, R1105, R1106, R1107, R1108, R1109, R1110, R1111, R1112, R1512",0402,13,22R,C25092
R1125,0402,1,220R,C25091
R1401,0402,1,240R 1%,C25094
R1505,0402,1,24R9,C5099
"R1506, R1509",0402,2,240R,C25094
"R1507, R1510",0402,2,26R1,C25098
"R1513, R1514",0402,2,49R9,C25120
R201,0402,1,487k,C27010
R202,0402,1,68k1,C11537
R205,0402,1,7k68,C25919
"R206, R209",0402,2,10k2,C11660
R208,0402,1,19k1,C52036
R211,0402,1,75k,C25798
R212,0402,1,20k,C25765
R301,0402,1,18k7,C11476
R302,0402,1,15k,C25756
R303,0402,1,35k7,C26975
R304,0402,1,11k5,C270653
"R401, R403",0402,2,0R,C17168
R409,0402,1,64k9,C26984
R411,0402,1,20k5 0.1%,C723525
R412,0402,1,14k7 0.1%,C281774
"R413, R414, R415, R416, R417",R_0612_Rohm_LTR18,5,0R1,C426512
R701,0402,1,2k4,C25882
"R801, R802, R901, R902",0402,4,5k1,C25905
R803,0402,1,4k7 1%,C25900
R804,0402,1,10k 1%,C25744
"R806, R906",0402,2,12k 1%,C25752
"R811, R910",0402,2,2k2,C25879
R903,0402,1,27R,C25100
R904,0402,1,39k,C25783
SW1001,SW_SPDT_Shouhan_MSK12C02,1,TCXO / EXT,C431540
SW1101,SW_SP3T_Shouhan_MSK13C02_Edge,1,JTAG-OFF-SERIAL,C2681567
SW1201,SW_Push_1P1T_XKB_TS-1187A,1,RESET,C318884
SW201,SW_SPDT_Shouhan_MSK12C02,1,POWER on / off,C431540
SW401,SW_Slide_DPDT_CK_1201M2_E-Switch_500SDP1_P4.70x4.83mm,1,INT / EXT,C273377
SW701,SW_SPDT_Shouhan_MSK12C02,1,M2,C431540
SW702,SW_SPDT_Shouhan_MSK12C02,1,M1,C431540
SW703,SW_SPDT_Shouhan_MSK12C02,1,M0,C431540
SW704,SW_Push_1P1T_XKB_TS-1187A,1,PROG,C318884
TP1001,TestPoint_Keystone_5005-5009_Compact_NoCircle,1,OUT0,Keystone 5008 (orange)
TP1002,TestPoint_Keystone_5005-5009_Compact_NoCircle,1,OUT1_N,Keystone 5008 (orange)
TP1003,TestPoint_Keystone_5005-5009_Compact_NoCircle,1,OUT4_N,Keystone 5008 (orange)
TP1004,TestPoint_Keystone_5005-5009_Compact_NoCircle,1,REF_CLK,Keystone 5008 (orange)
"TP1005, TP1202, TP1503, TP403, TP704",TestPoint_Keystone_5005-5009_Compact_NoCircle,5,GND,C2906764
TP1201,TestPoint_Keystone_5005-5009_Compact_NoCircle,1,TRIGGER,Keystone 5008 (orange)
TP1501,TestPoint_Keystone_5005-5009_Compact_NoCircle,1,LNA1,C238126
TP1502,TestPoint_Keystone_5005-5009_Compact_NoCircle,1,LNA2,C238126
TP401,TestPoint_Keystone_5005-5009_Compact_NoCircle,1,VCCINT,C2906763
TP402,TestPoint_Keystone_5005-5009_Compact_NoCircle,1,VCCINT_SRC,C2906763
TP701,TestPoint_Keystone_5005-5009_Compact_NoCircle,1,PROGRAM_B,C238125
TP702,TestPoint_Keystone_5005-5009_Compact_NoCircle,1,INIT_B,C238125
TP703,TestPoint_Keystone_5005-5009_Compact_NoCircle,1,DONE,C238125
U1,AMD_SBVA1024_BGA-1024_27.0x27.0mm_Layout32x32_P0.8mm,1,XCSU200P-SBVA1024,
U1001,SOT-23-5,1,74LVC1G17,C7836
U1002,SOT-363_SC-70-6,1,74LVC1G157,C135822
U1003,Texas_RGE0024P_VQFN-24-1EP_4x4mm_P0.5mm_EP2.7x2.7mm_ThermalVias,1,CDCE6214RGER,C3608351
U1004,SOT-23-5,1,74LVC1G125,C23654
"U1101, U1102, U803",TSSOP-14_4.4x5mm_P0.65mm,3,74LVC125,C7813
U1103,TSSOP-14_4.4x5mm_P0.65mm,1,SN74LV4T125,C90755
"U1501, U303",SOT-23-5,2,TPS7A2033PDBVR,C2862740
"U1502, U1503",WSON-8-1EP_3x3mm_P0.5mm_EP1.6x2.0mm,2,LMH6629SD,C2060235
"U201, U202, U203",SOT-583-8,3,TPS62933F,C5219272
"U301, U302",Texas_S-PDSO-N10_EP1.2x2mm_ThermalVias,2,TPS7A9101,C2878140
U304,SOT-23-5,1,TPS7A2012PDBVR,C2864597
U401,QFN-20-1EP_3.5x3.5mm_P0.5mm_EP2x2mm_ThermalVias,1,TPS7A8400ARGRR,C524802
U402,TSOT-23-6,1,TPS3700DDCR,C33002
U701,WSON-8-1EP_6x5mm_P1.27mm_EP3.4x4.3mm,1,W25Q256JWPIQ,C5362614
"U702, U804",SOT-23-5,2,SN74LV1T125DBV,C473338
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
